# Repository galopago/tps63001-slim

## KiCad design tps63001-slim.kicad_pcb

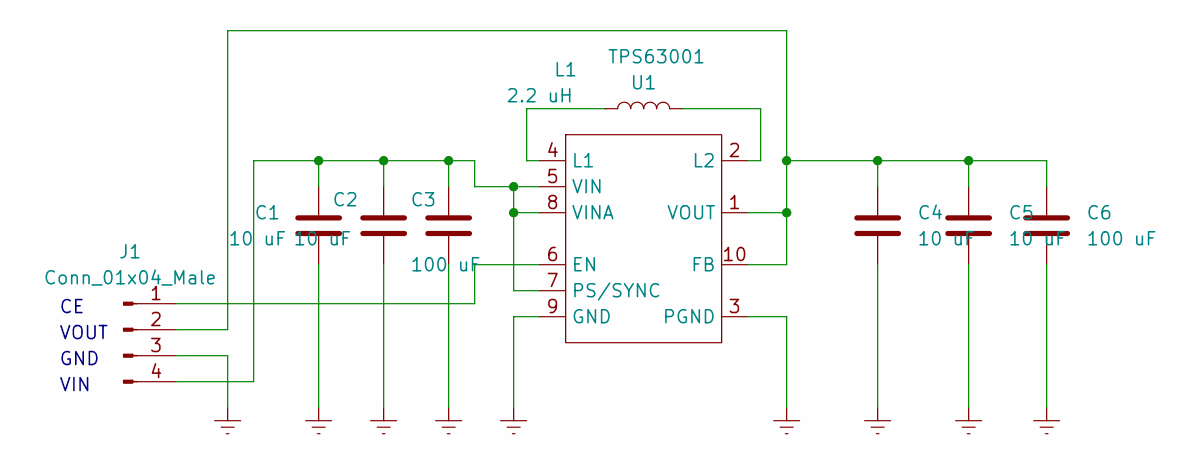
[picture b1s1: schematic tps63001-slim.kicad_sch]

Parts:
C1, C2, C4, C5: 10 uF; C_0805_2012Metric_Pad1.18x1.45mm_HandSolder
C3, C6: 100 uF; CP_EIA-3528-21_Kemet-B_Pad1.50x2.35mm_HandSolder
J1: Conn_01x04_Male; PinHeader_1x04_P2.54mm_Vertical
L1: 2.2 uH; L_Ferrocore_narrow_DLG-0504
U1: TPS63001; VSON-10-1EP_3x3mm_P0.5mm_EP1.2x2mm_ThermalVias

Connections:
Earth: C1.2, C2.2, C3.2, C4.2, C5.2, C6.2, J1.3, U1.3 (PGND), U1.9 (GND), U1.11 (PGND)
unnamed: C1.1, C2.1, C3.1, J1.4, U1.5 (VIN), U1.7 (PS/SYNC), U1.8 (VINA)
unnamed: C4.1, C5.1, C6.1, J1.2, U1.1 (VOUT), U1.10 (FB)
unnamed: J1.1, U1.6 (EN)
unnamed: L1.1, U1.4 (L1)
unnamed: L1.2, U1.2 (L2)

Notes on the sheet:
VOUT
VIN
GND

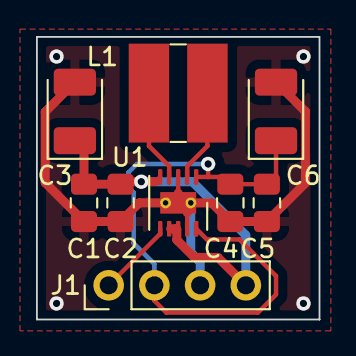
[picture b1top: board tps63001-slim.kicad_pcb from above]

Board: 2 copper layers, 15.7 x 15.7 mm, 9 parts (0 on the bottom side), 6 nets.

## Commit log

2023-11-05 all components placed
2023-11-05 board routed
2023-11-05 single gerber
